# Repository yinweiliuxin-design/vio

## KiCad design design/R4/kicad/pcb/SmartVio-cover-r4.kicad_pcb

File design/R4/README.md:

# SmartVio R4 设计方案

在线版（含效果图）：https://claude.ai/artifact/BZ7bgUTucvGM85bej3NQhv ，本地 `report/index.html`。

装琴效果图：`report/img/r4-on-violin-showcase.jpg`（你的实拍琴 + R4 模块按 3.18 px/mm 合成）。整机方案（琴 + 模块 + App）：https://claude.ai/artifact/1Rpw8Ssot14Bnj9UHH1J9D

基线是 R3 完整交付包和 `review/R3-2026-10-13/` 的两轮审核。R4 只做让样机装得上、能出声、能安全充电、日常好用的修改，不加功能、不换架构、不加芯片。原 R3 文件一律未改。

| 路径 | 内容 | 状态 |
|---|---|---|
| `DECISIONS.md` | 7 个待定问题的定案 | 定稿 |
| `checks/` | PCM1864 时钟与 SAI、电源 IC 逐脚与封装核对 | 完成 |
| `mechanical/` | 改好的 CadQuery 源、R3→R4 补丁、零件 STEP、装配扫掠结果、`CHANGES.md` | 已重建，0 干涉 |
| `firmware/` | R3→R4 补丁、改动源码、Linux 构建脚本、ELF/BIN/MAP、`CHANGES.md` | 已编译，主机测试全过，硬件测试 0 |
| `eco/` | 原理图 ECO（E-01…E-14）、PCB/FPC ECO（L-01…L-22） | 待在 KiCad 10 执行并跑 ERC/DRC |
| `report/` | 设计方案页与 5 张效果图 | — |
| `tools/` | `photo_r4.html` + `shot_alpha.cjs` 渲染模块俯视透明图，`composite_r4.py <照片> <模块图> <输出目录>` 合成装琴效果图；渲染：`step2mesh.cjs <mechanical 目录> r4mesh` 生成网格，`real_r4.html?view=hero|exploded|internal|section|product` | — |

## 还需要做的事

1. 用万用表量 Kycon STX-353K7A-6N：插入 TRS 插头前后 4–5、5–6 是否导通，决定 R323 和固件 `HP_DETECT_ACTIVE_HIGH`。
2. 在 KiCad 10 执行两份 ECO，跑 ERC/DRC/原理图一致性；画 KEYS6、USB16、AUDIO4 FPC 平面图并做纸样。
3. 用 ESP-IDF 5.4.3 重编 ESP32（需补 sdkconfig）；首次配对新耳机需在 ESP32 加搜索和 NVS 保存。
4. 首样台架：FW-RESET-KILL、续航与关机电流、卡扣/按键/异响/插拔力、扬声器音量。
5. 结构：最坏尺寸链、工程图重出、NTC 预压、琴腔配钻。

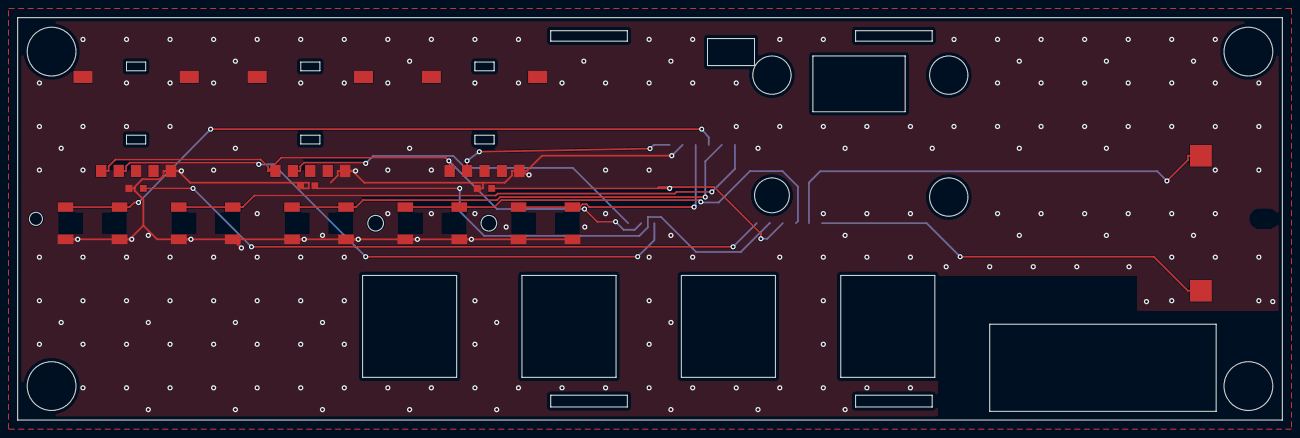
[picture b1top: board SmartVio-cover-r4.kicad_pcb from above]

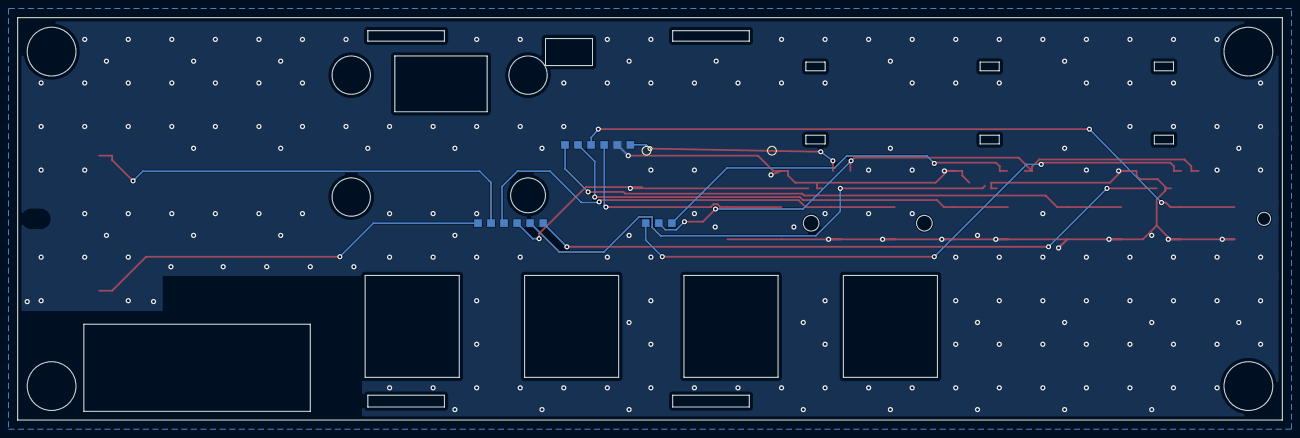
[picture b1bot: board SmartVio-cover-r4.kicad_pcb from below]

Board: 2 copper layers, 145.2 x 46.2 mm, 23 parts (3 on the bottom side), 15 nets.

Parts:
D850, D851, D852: APT1608VRCXF/A-5MAV; LED_Kingbright_APT1608VRCXF_A_5MAV
H901, H902: NPTH_D1.8
H903, H904, H906: NPTH_D4.4_KO5.4
H905: NPTH_D4.0_KO5.0
H907: NPTH_D1.5
H908: SLOT_2.5x1.5
J3406: KEYS6 remote-end FPC landing (H_COVER_1_R); WirePads_6_P1.5
J3408: COVER6 remote-end FPC landing (H_COVER_2_R); WirePads_6_P1.5
J3410: POTS3 remote-end FPC landing (H_COVER_3_R); WirePads_3_P1.5
LS901: AS01808AO-SC18-WP-R; Speaker_PUI_AS01808AO_SC18_Spring_REFERENCE
RV810, RV811, RV812: RK10J11R0A0L; Pot_Alps_RK10J11R0A0L
SW810, SW811, SW812, SW813, SW814: SKQGABE010; Switch_Alps_SKQGABE010

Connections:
FX_RAW: J3406.1, RV812.2 (WIPER)
GND: D850.1 (K), D851.1 (K), D852.1 (K), J3406.2, RV810.3 (LOW), RV811.3 (LOW), RV812.3 (LOW), SW810.3 (B1), SW810.4 (B2), SW811.3 (B1), SW811.4 (B2), SW812.3 (B1), SW812.4 (B2), SW813.3 (B1), SW813.4 (B2), SW814.3 (B1), SW814.4 (B2)
KEY_BT: J3406.3, SW814.1 (A1), SW814.2 (A2)
KEY_FX: J3406.4, SW810.1 (A1), SW810.2 (A2)
KEY_MIX: J3406.5, SW812.1 (A1), SW812.2 (A2)
KEY_MODE: J3406.6, SW811.1 (A1), SW811.2 (A2)
LED_ZONE_1_A: D850.2 (A), J3408.1
LED_ZONE_2_A: D851.2 (A), J3408.2
LED_ZONE_3_A: D852.2 (A), J3408.3
PWR_PB: J3408.4, SW813.1 (A1), SW813.2 (A2)
SPK_N: J3408.5, LS901.2 (-)
SPK_P: J3408.6, LS901.1 (+)
TONE_RAW: J3410.1, RV811.2 (WIPER)
V3D: J3410.2, RV810.1 (HIGH), RV811.1 (HIGH), RV812.1 (HIGH)
VOL_RAW: J3410.3, RV810.2 (WIPER)

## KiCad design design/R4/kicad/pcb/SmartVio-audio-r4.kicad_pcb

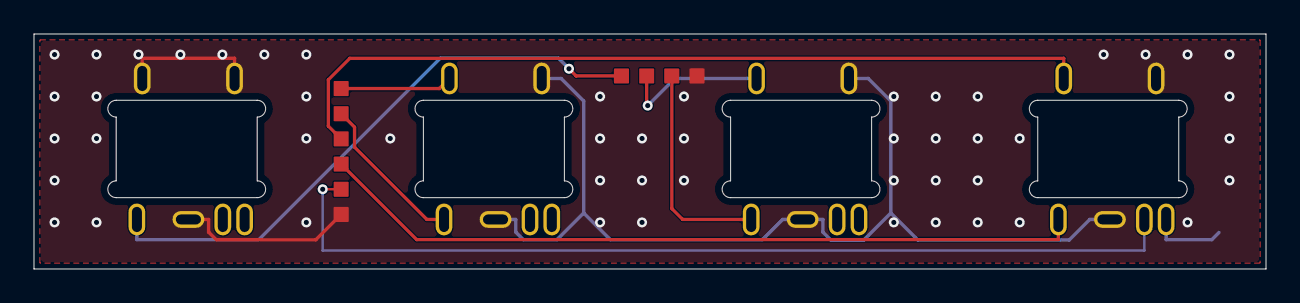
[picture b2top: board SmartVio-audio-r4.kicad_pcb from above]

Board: 2 copper layers, 73.4 x 14.0 mm, 7 parts (1 on the bottom side), 10 nets.

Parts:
J102, J201, J202, J301: STX-353K7A-6N-KTTR; Jack_Kycon_STX353K7A6N
J3402: AUDIO6 remote-end FPC landing (H_AUDIO_1_R); WirePads_6_P1.5
J3404: AUDIO4 remote-end FPC landing (H_AUDIO_2_R); WirePads_4_P1.5
R323: 0R; R_0603_1608Metric

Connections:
GND: J102.1 (SLEEVE), J102.2 (RING2_TRS_SLEEVE), J102.3 (RING1), J201.1 (SLEEVE), J201.2 (RING2_TRS_SLEEVE), J202.1 (SLEEVE), J202.2 (RING2_TRS_SLEEVE), J301.1 (SLEEVE), J301.2 (RING2_TRS_SLEEVE), J3402.1, J3404.4, R323.2
HP_DETECT_RAW: J301.5 (DET_NO_A), J3402.2
HP_DET_B: J301.6 (DET_NO_B), R323.1
HP_L_PORT: J301.4 (TIP), J3402.3
HP_R_PORT: J301.3 (RING1), J3402.4
LINE_L_PORT: J201.4 (TIP), J3402.5
LINE_R_PORT: J201.3 (RING1), J3402.6
RETURN_L_PORT: J202.4 (TIP), J3404.1
RETURN_R_PORT: J202.3 (RING1), J3404.2
SEND_T_PORT: J102.4 (TIP), J3404.3

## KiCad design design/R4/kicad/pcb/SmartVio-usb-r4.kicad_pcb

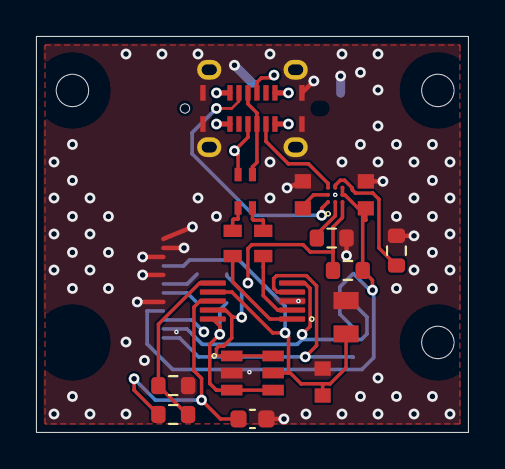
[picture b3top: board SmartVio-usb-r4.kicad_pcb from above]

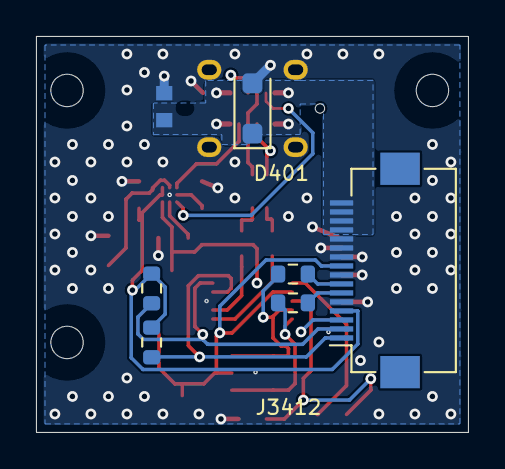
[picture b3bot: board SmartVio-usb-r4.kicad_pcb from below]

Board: 4 copper layers, 24.0 x 22.0 mm, 28 parts (7 on the bottom side), 24 nets.

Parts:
C401, C1401: 100nF / 50V X7R; CC0603KRX7R9BB104
C403: 100nF / 10V X7R; local U401.5 bypass; CC0603KRX7R7BB104
C1402: 1uF / 10V; CC0603KRX7R7BB105
C1501: 2.2uF 16V X7R; effective 1..10uF; CC0805KKX7R7BB225
C1502: 1uF 10V X7R; effective 0.3..3uF; C_0603_1608Metric
D401: SMF12A; D_SOD-123F
FL1501: 90 ohm at 100MHz candidate; ACM2012H-900-2P-T06
H401, H402, H403: NPTH 1.8 KO 4.4; NPTH_D1.8_KO4.4
J401: USB4120-03-C; GCT_USB4120_Official_A6
J3412: FH12-16S-0.5SH(55); Hirose_FH12-16S-0.5SH_1x16-1MP_P0.50mm_Horizontal
KO401: KEEPOUT 4.4 F; KEEPOUT_D4.4_F
L1501, L1502: 10nH matched candidate; 0603HP-10NXGRW
R401, R402: 5.1k; R_0603_1608Metric
R403, R404: 0R / tune at PHY; R_0603_1608Metric
R1401, R1502, R1503: 100k; R_0603_1608Metric
R1501: 24.9k 1%; R_0603_1608Metric
R1504: 140k 1%; R_0603_1608Metric
U401: USBLC6-2SC6; ST_USBLC6_2SC6_SOT23_6L_Official
U1401: TPD2S300YFFR; TI_YFF0009_Official
U1501: TPD2S703QDGSRQ1; TI_DGS0010A_Official

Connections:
CC1_PORT: J401.A5 (CC1), U1401.A1 (C_CC1)
CC1_SAFE: R401.1, U1401.B1 (CC1)
CC2_PORT: J401.B5 (CC2), U1401.A3 (C_CC2)
CC2_SAFE: R402.1, U1401.B3 (CC2)
CC_FAULT_N: J3412.3, R1401.1, U1401.C1 (FLT_N)
CC_VBIAS: C1401.1, U1401.A2 (VBIAS)
GND: C401.2, C403.2, C1401.2, C1402.2, C1501.2, C1502.2, D401.2, J401.A1 (GND), J401.A12 (GND), J401.B1 (GND), J401.B12 (GND), J401.SH (SHELL), J3412.5, J3412.8, J3412.10, J3412.11, J3412.12, R401.2, R402.2, R1501.2, U401.2 (GND), U1401.B2 (GND), U1501.3 (GND)
USB_5V_SAFE: C403.1, C1501.1, J3412.9, U401.5 (VBUS), U1501.7 (VPWR)
USB_DATA_DISABLE: J3412.2, R1502.1, U1501.5 (EN_N)
USB_DATA_FAULT_N: J3412.1, R1503.1, U1501.4 (FLT_N)
USB_DM_CMC: FL1501.3 (DM_OUT), L1502.1
USB_DM_CONN: FL1501.2 (DM_IN), J401.A7 (D-), J401.B7 (D-)
USB_DM_MCU: J3412.6, R404.2
USB_DM_OVP_IN: L1502.2, U1501.1 (VD_MINUS)
USB_DM_SYS: R404.1, U401.3 (IO2), U401.4 (IO2), U1501.10 (D_MINUS)
USB_DP_CMC: FL1501.4 (DP_OUT), L1501.1
USB_DP_CONN: FL1501.1 (DP_IN), J401.A6 (D+), J401.B6 (D+)
USB_DP_MCU: J3412.7, R403.2
USB_DP_OVP_IN: L1501.2, U1501.2 (VD_PLUS)
USB_DP_SYS: R403.1, U401.1 (IO1), U401.6 (IO1), U1501.9 (D_PLUS)
USB_OVP_MODE: R1501.1, R1504.2, U1501.6 (MODE)
USB_VREF: C1502.1, R1504.1, U1501.8 (VREF)
V3D: C1402.1, J3412.4, R1401.2, R1502.2, R1503.2, U1401.C2 (VPWR), U1401.C3 (VM)
VBUS_RAW: C401.1, D401.1, J401.A4 (VBUS), J401.A9 (VBUS), J401.B4 (VBUS), J401.B9 (VBUS), J3412.13, J3412.14, J3412.15, J3412.16

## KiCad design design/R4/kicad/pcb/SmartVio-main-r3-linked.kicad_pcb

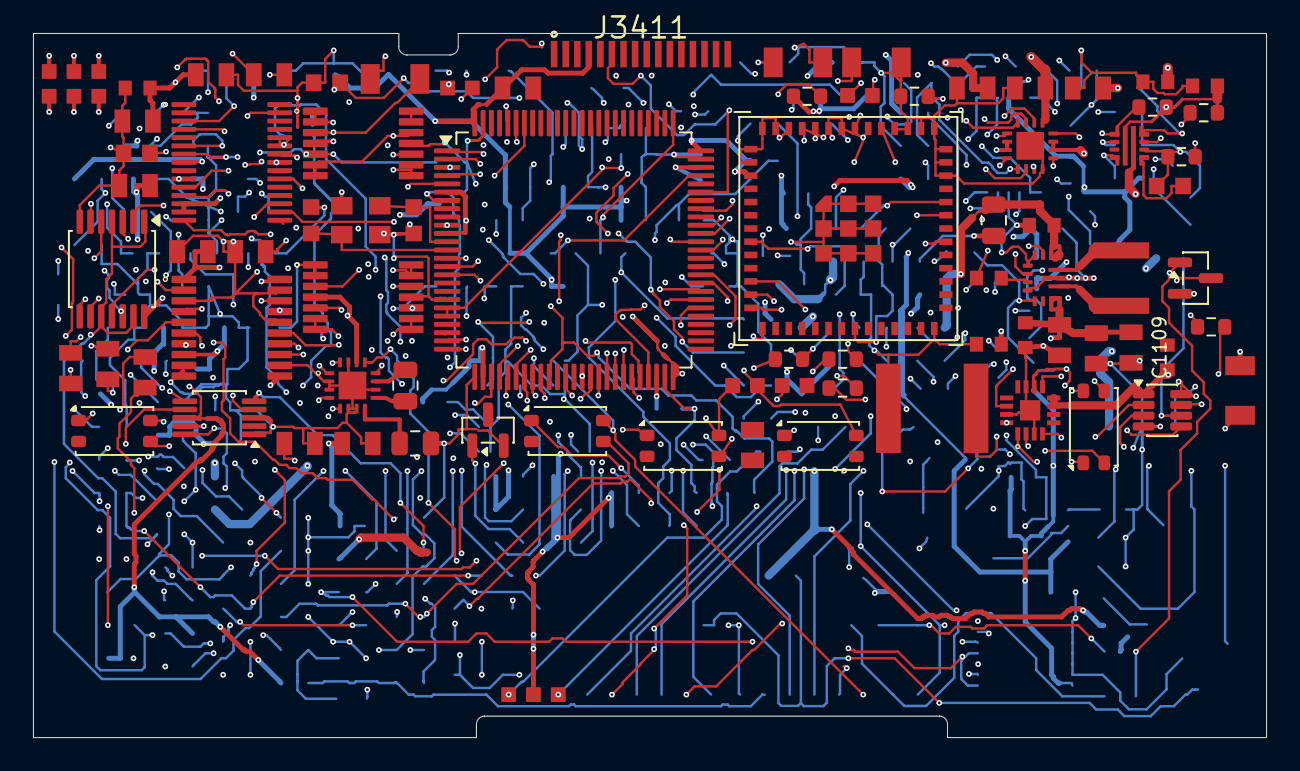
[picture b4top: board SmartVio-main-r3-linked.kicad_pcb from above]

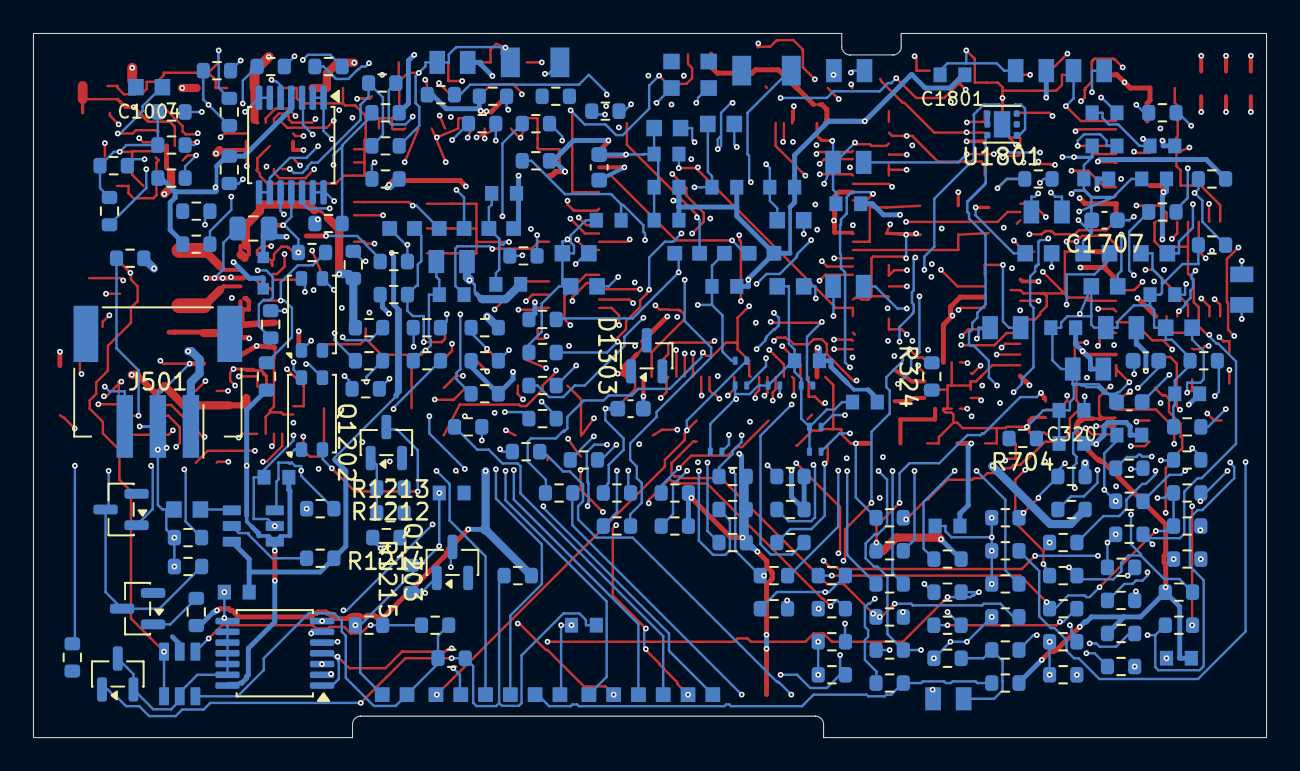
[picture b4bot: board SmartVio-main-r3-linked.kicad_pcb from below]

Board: 8 copper layers, 74.6 x 42.6 mm, 295 parts (217 on the bottom side), 216 nets.

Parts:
C101, C811, C830, C831, C832, C1302: 0.1uF C0G 25V 5%; C1206C104J3GACTU
C102: 10uF / 10V; CC0805KKX5R6BB106
C103, C240, C307, C1301: 100nF / 10V; CC0603KRX7R7BB104
C104, C111, C201, C202, C231, C232, C241, C301, C302: 1uF / 10V; CC0805KKX7R7BB105
C121, C211, C212, C502, C503: 10uF / 10V effective >=4.7uF; CC0805KKX5R6BB106
C221, C222: 4.7uF / 10V; CC0805KKX7R6BB475
C303: 1uF / 10V; C_0805_2012Metric
C304: 2.2uF / 10V X7R; Ceff_min >= C303_Ceff_max; C_0805_2012Metric
C305, C306: 2.2uF / 10V; CC0805KKX7R7BB225
C320: 100nF X7R 10V; CC0603KRX7R7BB104
C501: 4.7uF / 10V effective >=1uF; CC0805KKX7R6BB475
C601, C810, C901: 1uF; CC0603KRX7R7BB105
C602, C604, C606, C608, C703, C710, C712, C714, C801, C802, C803, C804, C805, C809, C902, C904, C1101, C1103, C1107, C1108: 100nF; CC0603KRX7R7BB104
C603, C605, C607, C711, C713, C715, C905: 10uF; CC0805KKX5R6BB106
C701, C702: 2.2uF; C_0603_1608Metric
C704, C705: 0.0022uF C0G 50V 5%; C0603C222J5GACTU
C806: 4.7uF; CC0805KKX7R6BB475
C807, C808: 2.2uF low ESR; C_0603_1608Metric
C812, C813: 3e-05uF C0G 50V 5%; C0603C300J5GACTU
C820: 0.001uF C0G 50V 5%; C0603C102J5GACTU
C821, C822, C823, C824, C825, C1004, C1701, C1702, C1703, C1704, C1705, C1706, C1708, C1901: 0.01uF C0G 25V 5%; C0603C103J3GACTU
C903: 22uF; CC0805MKX5R6BB226
C1001: 0.0047uF C0G 50V 5%; C0603C472J5GACTU
C1002: 100nF 50V; CC0603KRX7R9BB104
C1003: 1uF 16V; CC0603KRX7R7BB105
C1102: 10uF 10V; C_0805_2012Metric
C1104, C1105, C1109: 22uF 10V; CC0805MKX5R6BB226
C1106: 22uF 10V; C_0805_2012Metric
C1303: 0.47uF C0G 50V 5%; C2220C474J5GACTU
C1707: 100pF C0G 50V 5%; C_0603_1608Metric
C1709, C1710, C1711, C1801: 100nF 10V X7R; CC0603KRX7R7BB104
C1902: 2.2uF X7R 16V; effective>=1uF; CC0603KRX7R7BB225
C1903, C1904, C1921, C1922: 100nF X7R 16V; CC0603KRX7R7BB104
D1201, D1202, D1203, D1204, D1205, D1206, D1207: TPD1E10B06DPYR; TI_DPY0002A_1x0.6mm_P0.7mm_NSMD
D1301, D1302: low-leakage enable OR; SOT-23
D1303: BAS116,215; SOT-23
FB1101: Ferrite 120R@100MHz / >=0.5A; 742792625
J101: Existing pickup / polarity TBD; WirePads_2_P1.5
J501: JST PH 3-way internal2A AWG24 pack header; JST_PH_S3B_PH_SM4_TB_OfficialLand_3P
J801: SWD test pads; WirePads_5_P1.5
J901: Speaker harness; WirePads_2_P1.5
J902: RF factory pads - not user connector; WirePads_6_P1.5
J1921: RT1921 harness solder endpoint; WirePads_2_P1.5
J3401: AUDIO6 main-end FPC landing (H_AUDIO_1_M); WirePads_6_P1.5
J3403: AUDIO4 main-end FPC landing (H_AUDIO_2_M); WirePads_4_P1.5
J3405: KEYS6 main-end FPC landing (H_COVER_1_M); WirePads_Control6_2x3_R3
J3407: COVER6 main-end FPC landing (H_COVER_2_M); WirePads_6_P1.5
J3409: POTS3 main-end FPC landing (H_COVER_3_M); WirePads_3_P1.5
J3411: USB16 main-end hot-bar landing (J_USB_M); FPC_USB16_HotBar_Main_P0.70
K1201, K1202: AQY221R6VY; Panasonic_APV-AQY_SSOP-4_4.45x2.65mm_P1.27mm
K1203, K1204, K1205, K1206, K1207: AQY221R2VY; Panasonic_APV-AQY_SSOP-4_4.45x2.65mm_P1.27mm
L1101: 1.5uH / Isat >=5A candidate; XGL4020-152MEC
Q1201, Q1202, Q1203: PMV30UN2R; SOT-23
Q1601: PMV30UN2; SOT-23
R101, R103, R104, R201, R202, R241, R242, R311, R312, R503, R504, R802, R803, R820, R821, R822, R823, R824, R826, R901, R902, R1002, R1004, R1301: 10k; R_0603_1608Metric
R102: 4.7M; R_0603_1608Metric
R111: 100; R_0603_1608Metric
R121, R211, R212: 220; R_0603_1608Metric
R122, R221, R222, R320, R321, R322, R505, R506, R590, R703, R816, R817, R903, R904, R1006, R1104, R1211, R1213, R1215, R1302, R1602: 100k; R_0603_1608Metric
R231, R232, R301, R302: 22k; R_0603_1608Metric
R290, R291: 15k; R_0603_1608Metric
R324, R704, R830, R831, R832, R850, R851, R852, R1210, R1212, R1214, R1603, R1604: 1k; R_0603_1608Metric
R501: 2000ohm 0.1% 25ppm/C; R_0603_1608Metric
R502: 1500ohm 0.1% 25ppm/C; R_0603_1608Metric
R601: 0R; R_0603_1608Metric
R602, R603: 4.7k; R_0603_1608Metric
R691, R810, R811, R812, R813, R814, R815, R906: 33R initial; R_0603_1608Metric
R701, R702, R907: 470R; R_0603_1608Metric
R801: 10R; R_0603_1608Metric
R905: 2k; R_0603_1608Metric
R1001: 26.1k; R_0603_1608Metric
R1003: 39.2k 1%; R_0603_1608Metric
R1005: 2.49k 1%; R_0603_1608Metric
R1101: 312k; 0.1%; <=25ppm/K; exact MPN pending; R_0603_1608Metric
R1102: 100k; 0.1%; <=25ppm/K; exact MPN pending; R_0603_1608Metric
R1103, R1705, R1709: 2.2M 1%; R_0603_1608Metric
R1201, R1202, R1203, R1204, R1205, R1206, R1207: 390R; R_0603_1608Metric
R1303: 33k 1%; R_0603_1608Metric
R1304: 4.7M 1%; R_0603_1608Metric
R1601: 4.7k 1%; R_0603_1608Metric
R1701: 15k 0.1% 25ppm/C; R_0603_1608Metric
R1702: 10k 0.1% 25ppm/C; R_0603_1608Metric
R1703: 100k 0.1% 25ppm/C; R_0603_1608Metric
R1704, R1708, R1712, R1716: 100R 1%; R_0603_1608Metric
R1706, R1710: 1.5M 1%; R_0603_1608Metric
R1707, R1711: 10M 1%; R_0603_1608Metric
R1715: 10M; 1%; ISET buffer bias, include in mirror cali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; R_0603_1608Metric
R1717, R1911, R1913, R1922: 100k 1%; R_0603_1608Metric
R1801, R1802: 33R 1%; R_0603_1608Metric
R1901, R1902, R1903, R1912: 1k 1%; R_0603_1608Metric
R1921: 158k 1%; R_0603_1608Metric
R1923: 8.2k 1%; R_0603_1608Metric
R1924: 30.1k 1%; R_0603_1608Metric
R2351: 3.32k 0.1% 25ppm/C; R_0603_1608Metric
R2352: 68100ohm 0.1% 25ppm/C; R_0603_1608Metric
U101, U201: TLV9064PWR; TI_PW0014A_Official
U301: TPA6132A2RTER; TI_RTE0016C_Official
U501: BQ24074RGTR; TI_RGT0016C_BQ24074_EP17
U601: PCM1864DBTR; TI_DBT0030A_Official
U701: PCM5102APWR; TI_PW0020A_Official
U801: STM32H743VIT6; LQFP-100_14x14mm_P0.5mm
U901: ESP32-MINI-1U
U902: MAX98357AETE+; ADI_T1633_4_Official
U1001: TPS259470LRPWR; TI_RPW0010A_TPS259470
U1101: TPS63070RNMR; TI_RNM0015A_TPS63070
U1301: LTC2954ITS8-1#TRPBF; TSOT-23-8
U1701: ADS1115IDGSR; MSOP-10_3x3mm_P0.5mm
U1702: TMUX1511PWR; TSSOP-14_4.4x5mm_P0.65mm
U1703: OPA4330AIPWR; TSSOP-14_4.4x5mm_P0.65mm
U1801: TMP117AIDRVR; WSON-6-1EP_2x2mm_P0.65mm_EP1x1.6mm
U1901: sequenced performance-domain supply; TI_DBV0006A_Official
U1902: audio I2C powered-domain isolation; TSSOP-14_4.4x5mm_P0.65mm
U1921: independent pack NTC window inhibits charge gate; TI_DDC0006A_Official
U1922: 2.5V independent NTC excitation reference; SOT-23
Y801: 24.576MHz CL18pF candidate; ABM8-24_576MHZ-B2-T

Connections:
ADC_1V8: C602.1, C603.1, U601.11 (LDO)
ADC_AUX_L_AC: C231.2, U601.4 (VINR1)
ADC_AUX_R_AC: C232.2, U601.29 (VINL3)
ADC_BCK: R811.2, U601.17 (BCK)
ADC_BCK_SRC: R811.1, U801.4 (PE5_SAI1SCK)
ADC_DATA: U601.18 (DOUT), U801.5 (PE6_SAI1SD)
ADC_DATA2: R691.2, U801.2 (PE3_SAI1_SD_B)
ADC_DATA2_SRC: R691.1, U601.21 (GPIO1)
ADC_FS: R810.2, U601.16 (LRCK)
ADC_FS_SRC: R810.1, U801.3 (PE4_SAI1FS)
ADC_PU_AC: C111.2, U601.3 (VINL1)
ADC_SCK: R812.2, U601.15 (SCKI)
ADC_SCK_SRC: R812.1, U801.66 (PC9_MCO2)
ADC_VREF: C601.1, U601.6 (VREF)
ADC_XI: R601.1, U601.10 (XI)
AUDIO_BUS_EN: R1913.1, U801.7 (PC13), U1902.1 (SEL1), U1902.4 (SEL2)
AUDIO_PWR_EN: R1911.1, U801.1 (PE2_AUDIO_PWR_EN), U1901.3 (ON)
BOOT0: R803.1, U801.94 (BOOT0)
BUCK_AUX: C1101.1, U1101.3 (VAUX)
BUCK_FB: R1101.2, R1102.1, U1101.5 (FB)
BUCK_L1: L1101.1, U1101.11 (L1)
BUCK_L2: L1101.2, U1101.9 (L2)
CC_FAULT_N: J3411.3, U801.38 (PE8_CC_FAULT_N)
CELL_NTC_SENSE: J1921.1 (NTC_SENSE), R1921.1, R1924.2, U1921.3 (INA+)
CHARGE_ALLOW: R1601.1, U801.44 (PE14_CHARGE_ALLOW)
CHARGE_DISABLE: Q1601.3 (D), R503.2, U501.4 (CE)
CHARGE_GATE: Q1601.1 (G), R1601.2, R1602.1, U1921.1 (OUTA), U1921.6 (OUTB)
CHG_EN1: R590.1, R1603.2, U501.6 (EN1)
CHG_EN1_MCU: R1603.1, U801.42 (PE12_CHG_EN1)
CHG_EN2: R504.2, R1604.2, U501.5 (EN2)
CHG_EN2_MCU: R1604.1, U801.43 (PE13_CHG_EN2)
CHG_ITERM_ECO: R2351.1, U501.15 (ITERM)
CHG_PGOOD_N: R1902.2, U801.47 (PB11_CHG_PGOOD)
CHG_STATUS_N: R1903.2, U801.57 (PD10_CHG_STATUS)
CHG_TMR_ECO: R2352.1, U501.14 (TMR)
CHG_TP: R506.2, R1903.1, U501.9 (CHG)
DAC_1V8: C703.1, U701.18 (LDOO)
DAC_CPN: C701.2, U701.4 (CAPM)
DAC_CPP: C701.1, U701.2 (CAPP)
DAC_L: C201.1, C704.1, R301.1, R701.2
DAC_NEG: C702.1, U701.5 (VNEG)
DAC_R: C202.1, C705.1, R302.1, R702.2
DAC_RAW_L: R701.1, U701.6 (OUTL)
DAC_RAW_R: R702.1, U701.7 (OUTR)
DAC_UNMUTE: R703.1, R704.2, U701.17 (XSMT)
DAC_UNMUTE_MCU: R704.1, U801.22 (PA0)
EFUSE_DVDT: C1001.1, U1001.7 (DVDT)
EFUSE_ILM: R1005.1, U1001.9 (ILM)
EFUSE_ITIMER: C1004.1, U1001.10 (ITIMER)
FX_ADC: C832.1, R832.2, U801.16 (PC1_ADC123_INP11)
FX_RAW: J3405.1, R832.1
GND: C102.2, C103.2, C104.2, C240.2, C241.2, C304.2, C305.2, C306.2, C307.2, C320.2, C501.2, C502.2, C503.2, C601.2, C602.2, C603.2, C604.2, C605.2, C606.2, C607.2, C608.2, C702.2, C703.2, C704.2, C705.2, C710.2, C711.2, C712.2, C713.2, C714.2, C715.2, C801.2, C802.2, C803.2, C804.2, C805.2, C806.2, C807.2, C808.2, C809.2, C810.2, C811.2, C812.2, C813.2, C820.2, C821.2, C822.2, C823.2, C824.2, C825.2, C830.2, C831.2, C832.2, C901.2, C902.2, C903.2, C904.2, C905.2, C1001.2, C1002.2, C1003.2, C1004.2, C1101.2, C1102.2, C1103.2, C1104.2, C1105.2, C1106.2, C1107.2, C1108.2, C1109.2, C1301.2, C1302.2, C1303.2, C1701.2, C1702.2, C1703.2, C1704.2, C1705.2, C1706.2, C1707.2, C1708.2, C1709.2, C1710.2, C1711.2, C1801.2, C1901.2, C1902.2, C1903.2, C1904.2, C1921.2, C1922.2, D1201.2 (GND), D1202.2 (GND), D1203.2 (GND), D1204.2 (GND), D1205.2 (GND), D1206.2 (GND), D1207.2 (GND), J101.2, J501.2 (PACK-), J801.3 (GND), J902.2 (GND), J1921.2 (RETURN), J3401.1, J3403.4, J3405.2, J3411.5, J3411.8, J3411.10, J3411.11, J3411.12, Q1201.2 (S), Q1202.2, Q1203.2, Q1601.2 (S), R104.2, R122.2, R221.2, R222.2, R311.2, R312.2, R320.2, R501.2, R502.2, R504.1, R601.2, R703.2, R803.2, R817.2, R901.2, R904.2, R1002.2, R1004.2, R1005.2, R1102.2, R1211.2, R1213.2, R1215.2, R1302.2, R1304.2, R1602.2, R1702.2, R1703.2, R1706.2, R1707.2, R1710.2, R1711.2, R1715.2, R1717.2, R1911.2, R1913.2, R1922.2, R2351.2, R2352.2, U101.11 (V-), U201.11 (V-), U301.2 (INL+), U301.3 (INR+), U301.6 (G0), U301.7 (G1), U301.10 (PGND), U301.15 (SGND), U301.17 (PAD), U501.8 (VSS), U501.17 (PAD_GND), U601.7 (AGND), U601.12 (DGND), U601.25 (MS_AD), U601.26 (MD0), U701.3 (CPGND), U701.9 (AGND), U701.10 (DEMP), U701.12 (SCK), U701.16 (FMT), U701.19 (DGND), U801.10 (VSS), U801.19 (VSSA), U801.26 (VSS), U801.49 (VSS), U801.74 (VSS), U801.99 (VSS), U901.1 (GND), U901.2 (GND), U901.27 (GND), U901.38 (GND), U901.39 (GND), U901.40 (GND), U901.41 (GND), U901.42 (GND), U901.43 (GND), U901.44 (GND), U901.45 (GND), U901.46 (GND), U901.47 (GND), U901.48 (GND), U901.49 (GND), U901.50 (GND), U901.51 (GND), U901.52 (GND), U901.53 (GND), U901.54 (GND), U901.55 (GND), U902.3 (GND), U902.11 (GND), U902.15 (GND), U902.17 (PAD), U1001.8 (GND), U1101.1 (PS_SYNC), U1101.4 (GND), U1101.10 (PGND), U1101.15 (VSEL), U1301.4 (GND), U1701.1 (ADDR), U1701.3 (GND), U1702.7 (GND), U1703.11 (V_MINUS), U1801.2, U1901.2 (GND), U1902.7 (GND), U1902.8 (D3), U1902.9 (S3), U1902.10 (SEL3), U1902.11 (D4), U1902.12 (S4), U1902.13 (SEL4), U1921.2 (GND), U1922.2 (ANODE), U1922.3 (STAR_TIE_ANODE), Y801.2 (GND), Y801.4 (GND)
HP_ATT_L: C301.1, R301.2, R311.1
HP_ATT_R: C302.1, R302.2, R312.1
HP_CPN: C303.2, U301.9 (CPN)
HP_CPP: C303.1, U301.11 (CPP)
HP_DETECT_GPIO: C320.1, R322.2, U801.28 (PA4)
HP_DETECT_RAW: J3401.2, R321.2, R322.1
HP_EN_MCU: R324.1, U801.23 (PA1)
HP_EN_VALIDATED: R320.1, R324.2, U301.13 (EN)
HP_IN_L: C301.2, U301.1 (INL-)
HP_IN_R: C302.2, U301.4 (INR-)
HP_L: K1201.3 (LOAD_A), U301.16 (OUTL)
HP_L_PORT: D1201.1 (IO), J3401.3, K1201.4 (LOAD_B)
HP_NEG: C304.1, U301.8 (HPVSS)
HP_PORT_ENABLE: R1212.1, U801.61 (PD14)
HP_POS: C305.1, U301.12 (HPVDD)
HP_R: K1202.3 (LOAD_A), U301.5 (OUTR)
HP_R_PORT: D1202.1 (IO), J3401.4, K1202.4 (LOAD_B)
HSE_IN: C812.1, U801.12 (PH0_OSC), Y801.1 (X1)
HSE_OUT: C813.1, U801.13 (PH1_OSC), Y801.3 (X2)
I2C_AUDIO_SCL: U601.24 (SCL), U1902.6 (D2)
I2C_AUDIO_SDA: U601.23 (SDA), U1902.3 (D1)
I2C_SCL: R603.1, R1801.1, U801.95 (PB8_I2C1SCL), U1701.10 (SCL), U1902.5 (S2)
I2C_SDA: R602.1, R1802.1, U801.96 (PB9_I2C1SDA), U1701.9 (SDA), U1902.2 (S1)
KEY_BT: C825.1, J3405.3, R824.2, U801.15 (PC0_KEY_BT)
KEY_FX: C821.1, J3405.4, R820.1, U801.29 (PA5)
KEY_MIX: C823.1, J3405.5, R822.1, U801.31 (PA7)
KEY_MODE: C822.1, J3405.6, R821.1, U801.30 (PA6)
KEY_PWR: C824.1, R823.1, U801.32 (PC4), U1301.5 (INT_N)
LED_ZONE_1: R850.1, U801.63 (PC6)
LED_ZONE_1_A: J3407.1, R850.2
LED_ZONE_2: R851.1, U801.64 (PC7)
LED_ZONE_2_A: J3407.2, R851.2
LED_ZONE_3: R852.1, U801.65 (PC8)
LED_ZONE_3_A: J3407.3, R852.2
LINE_AC_L: C201.2, R290.1
LINE_AC_R: C202.2, R291.1
LINE_BIAS_L: R201.1, R290.2, U201.3 (IN+_A)
LINE_BIAS_R: R202.1, R291.2, U201.5 (IN+_B)
LINE_BUF_L: C211.1, U201.1 (OUT_A), U201.2 (IN-_A)
LINE_BUF_R: C212.1, U201.6 (IN-_B), U201.7 (OUT_B)
LINE_L: K1203.3 (LOAD_A), R211.2, R221.1
LINE_L_PORT: D1203.1 (IO), J3401.5, K1203.4 (LOAD_B)
LINE_OUT_AC_L: C211.2, R211.1
LINE_OUT_AC_R: C212.2, R212.1
LINE_R: K1204.3 (LOAD_A), R212.2, R222.1
LINE_R_PORT: D1204.1 (IO), J3401.6, K1204.4 (LOAD_B)
LOAD_CT: C1901.1, U1901.4 (CT)
LOAD_QOD: R1912.2, U1901.5 (QOD)
MCU_VDDA: C809.1, C810.1, R801.2, U801.20 (VREF+), U801.21 (VDDA)
MON_BAT_ADC: C1704.1, R1708.2, U1701.5 (AIN1)
MON_BAT_BUF: R1708.1, U1703.6 (IN_B_MINUS), U1703.7 (OUT_B)
MON_BAT_BUF_IN: C1703.1, R1707.1, U1702.6 (D2), U1703.5 (IN_B_PLUS)
MON_BAT_DIV: R1705.2, R1706.1, U1702.5 (S2)
MON_ENABLE: R1717.1, U801.46 (PB10_MON_ENABLE), U1702.1 (SEL1), U1702.4 (SEL2), U1702.10 (SEL3), U1702.13 (SEL4)
MON_ICHG_ADC: C1708.1, R1716.2, U1701.7 (AIN3)
MON_ICHG_BUF: R1716.1, U1703.13 (IN_D_MINUS), U1703.14 (OUT_D)
MON_ICHG_BUF_IN: C1707.1, R1715.1, U1702.11 (D4), U1703.12 (IN_D_PLUS)
MON_SYS_ADC: C1706.1, R1712.2, U1701.6 (AIN2)
MON_SYS_BUF: R1712.1, U1703.8 (OUT_C), U1703.9 (IN_C_MINUS)
MON_SYS_BUF_IN: C1705.1, R1711.1, U1702.8 (D3), U1703.10 (IN_C_PLUS)
MON_SYS_DIV: R1709.2, R1710.1, U1702.9 (S3)
MON_USB_ADC: C1702.1, R1704.2, U1701.4 (AIN0)
MON_USB_BUF: R1704.1, U1703.1 (OUT_A), U1703.2 (IN_A_MINUS)
MON_USB_BUF_IN: C1701.1, R1703.1, U1702.3 (D1), U1703.3 (IN_A_PLUS)
MON_USB_DIV: R1701.2, R1702.1, U1702.2 (S1)
NRST: C811.1, J801.5 (NRST), R802.1, U801.14 (NRST)
NTC_COLD_DIV: R1921.2, R1922.1, U1921.4 (INB-)
PACK_NTC: J501.3 (NTC), U501.1 (TS)
PACK_PLUS: C503.1, J501.1 (PACK+), R1705.1, U501.2 (BAT), U501.3 (BAT)
PGOOD_TP: R505.2, R1902.1, U501.7 (PGOOD)
PLAY_BCK: R815.2, U701.13 (BCK), U901.14 (IO26), U902.16 (BCLK)
PLAY_BCK_SRC: R815.1, U801.60 (PD13_SAI2SCK)
PLAY_DATA: R813.2, U701.14 (DIN), U901.33 (IO22)
PLAY_DATA_SRC: R813.1, U801.58 (PD11_SAI2SD)
PLAY_FS: R814.2, U701.15 (LRCK), U901.13 (IO25), U902.14 (LRCLK)
PLAY_FS_SRC: R814.1, U801.59 (PD12_SAI2FS)
PORT_ENABLE: R1210.1, U801.25 (PA3)
PU_ADC_COUPLE: C111.1, R111.2
PU_BIAS: C101.2, R102.1, U101.3 (IN+_A)
PU_BUF: R111.1, U101.1 (OUT_A), U101.2 (IN-_A), U101.10 (IN+_C)
PWR_BOOT_OK: R1301.1, U801.37 (PE7_BOOT_OK)
PWR_KILL: R1301.2, R1302.1, U1301.8 (KILL)
PWR_LTC_EN: D1301.1 (A), R1103.2, U1301.6 (EN)
PWR_ONT: C1302.1, U1301.3 (ONT)
PWR_PB: D1303.3, J3407.4, R826.2, U1301.2 (PB)
PWR_PB_SENSE: D1303.1, U801.51 (PB12)
PWR_PDT: C1303.1, U1301.7 (PDT)
PZ_LIMIT: C101.1, R101.2
PZ_RAW: J101.1, R101.1
RETURN_L: C221.1, K1206.3 (LOAD_A)
RETURN_L_PORT: D1206.1 (IO), J3403.1, K1206.4 (LOAD_B)
RETURN_R: C222.1, K1207.3 (LOAD_A)
RETURN_R_PORT: D1207.1 (IO), J3403.2, K1207.4 (LOAD_B)
RET_AC_L: C221.2, R231.1
RET_AC_R: C222.2, R232.1
RET_BIAS_L: R231.2, R241.1, U201.10 (IN+_C)
RET_BIAS_R: R232.2, R242.1, U201.12 (IN+_D)
RET_BUF_L: C231.1, U201.8 (OUT_C), U201.9 (IN-_C)
RET_BUF_R: C232.1, U201.13 (IN-_D), U201.14 (OUT_D)
RET_PORT_ENABLE: R1214.1, U801.62 (PD15)
RF_BOOT: J902.5 (BOOT), R902.1, U901.21 (IO0)
RF_CHIP_EN: C901.1, J902.6 (EN), R901.1, R907.2, U901.8 (EN)
RF_ENABLE: R907.1, U801.33 (PC5)
RF_PROG_RX: J902.3 (RX_IN), U901.35 (RXD0)
RF_PROG_TX: J902.4 (TX_OUT), U901.36 (TXD0)
RF_RX: U801.55 (PD8_USART3TX), U901.11 (IO32_UART_RX)
RF_TX: U801.56 (PD9_USART3RX), U901.12 (IO33_UART_TX)
RILIM: R502.1, U501.12 (ILIM)
RISET: R501.1, U501.16 (ISET), U1702.12 (S4)
SEND_AC: C121.2, R121.1
SEND_BUF: C121.1, U101.8 (OUT_C), U101.9 (IN-_C)
SEND_T: K1205.3 (LOAD_A), R121.2, R122.1
SEND_T_PORT: D1205.1 (IO), J3403.3, K1205.4 (LOAD_B)
SPK_DATA: R906.2, U902.1 (DIN)
SPK_DATA_SRC: R906.1, U801.41 (PE11_SAI2_SD_B)
SPK_ENABLE: R905.1, U801.24 (PA2)
SPK_GAIN: R903.1, U902.2 (GAIN_SLOT)
SPK_N: J901.2 (SPK-), J3407.5, U902.10 (OUTN)
SPK_P: J901.1 (SPK+), J3407.6, U902.9 (OUTP)
SPK_SD_PIN: R904.1, R905.2, U902.4 (SD_MODE)
SSR_GATE: Q1201.1 (G), R1210.2, R1211.1
SSR_GATE_HP: Q1202.1, R1212.2, R1213.1
SSR_GATE_RET: Q1203.1, R1214.2, R1215.1
SSR_LED_0: K1201.1 (LED_A), R1201.2
SSR_LED_1: K1202.1 (LED_A), R1202.2
SSR_LED_2: K1203.1 (LED_A), R1203.2
SSR_LED_3: K1204.1 (LED_A), R1204.2
SSR_LED_4: K1205.1 (LED_A), R1205.2
SSR_LED_5: K1206.1 (LED_A), R1206.2
SSR_LED_6: K1207.1 (LED_A), R1207.2
SSR_SINK: K1203.2 (LED_K), K1204.2 (LED_K), K1205.2 (LED_K), Q1201.3 (D)
SSR_SINK_HP: K1201.2 (LED_K), K1202.2 (LED_K), Q1202.3
SSR_SINK_RET: K1206.2 (LED_K), K1207.2 (LED_K), Q1203.3
SWCLK: J801.4 (SWCLK), U801.76 (PA14_SWCLK)
SWDIO: J801.2 (SWDIO), U801.72 (PA13_SWDIO)
SYS: C502.1, C904.1, C905.1, C1102.1, C1103.1, C1301.1, R503.1, R826.1, R903.2, R1103.1, R1709.1, U501.10 (OUT), U501.11 (OUT), U902.7 (VDD), U902.8 (VDD), U1101.12 (VIN), U1101.13 (VIN), U1301.1 (VIN)
SYS_ENABLE: D1301.3 (K), D1302.3 (K), R1304.1, U1101.14 (EN)
TEMP_REF2V5: C1922.1, R1923.2, R1924.1, U1922.1 (CATHODE)
TEMP_SCL: R1801.2, U1801.1
TEMP_SDA: R1802.2, U1801.6
TONE_ADC: C831.1, R831.2, U801.35 (PB1)
TONE_RAW: J3409.1, R831.1
UNUSED_BUF: U101.13 (IN-_D), U101.14 (OUT_D)
USB_5V_SAFE: C501.1, C1003.1, C1921.1, J3411.9, R816.1, R1303.1, R1701.1, R1923.1, U501.13 (IN), U1001.6 (OUT), U1921.5 (VDD)
USB_DATA_DISABLE: J3411.2, U801.40 (PE10_USB_DATA_DISABLE)
USB_DATA_FAULT_N: J3411.1, U801.39 (PE9_USB_DATA_FAULT_N)
USB_DM_MCU: J3411.6, U801.70 (PA11_USBDM)
USB_DP_MCU: J3411.7, U801.71 (PA12_USBDP)
USB_FLT: R1006.1, R1901.1, U1001.4 (FLT)
USB_FLT_MCU: R1901.2, U801.45 (PE15_USB_FLT)
USB_OV: R1003.2, R1004.1, U1001.2 (OVLO)
USB_UV: R1001.2, R1002.1, U1001.1 (EN_UVLO)
USB_WAKE_A: D1302.1 (A), R1303.2
V3A: C103.1, C104.1, C240.1, C241.1, C306.1, C307.1, C604.1, C605.1, C710.1, C711.1, C712.1, C713.1, C1106.1, C1107.1, FB1101.2, R103.1, U101.4 (V+), U201.4 (V+), U301.14 (VDD), U601.8 (AVDD), U701.1 (CPVDD), U701.8 (AVDD)
V3D: C801.1, C802.1, C803.1, C804.1, C805.1, C806.1, C902.1, C903.1, C1104.1, C1105.1, C1108.1, C1109.1, C1709.1, C1710.1, C1711.1, C1801.1, C1902.1, C1904.1, J801.1 (VTREF), J902.1 (3V3), J3409.2, J3411.4, R321.1, R505.1, R506.1, R590.2, R602.2, R603.2, R801.1, R802.2, R820.2, R821.2, R822.2, R823.2, R824.1, R902.2, R1006.2, R1101.1, R1104.2, R1201.1, R1202.1, R1203.1, R1204.1, R1205.1, R1206.1, R1207.1, U801.6 (VBAT), U801.11 (VDD), U801.27 (VDD), U801.50 (VDD), U801.75 (VDD), U801.100 (VDD), U901.3 (3V3), U1101.7 (VOUT), U1101.8 (VOUT), U1701.8 (VDD), U1702.14 (VDD), U1703.4 (V_PLUS), U1801.4, U1801.5, U1901.1 (VIN), U1902.14 (VDD)
V3LOAD: C606.1, C607.1, C608.1, C714.1, C715.1, C1903.1, FB1101.1, R1912.1, U601.13 (DVDD), U601.14 (IOVDD), U701.11 (FLT), U701.20 (DVDD), U1901.6 (VOUT)
V3_PG: R1104.1, U1101.2 (PG)
VBUS_RAW: C1002.1, J3411.13, J3411.14, J3411.15, J3411.16, R1001.1, R1003.1, U1001.5 (IN)
VBUS_SENSE: C820.1, R816.2, R817.1, U801.68 (PA9_VBUS)
VCAP1: C807.1, C808.1, U801.48 (VCAP1), U801.73 (VCAP2)
VMID: R102.2, R201.2, R202.2, R241.2, R242.2, U101.6 (IN-_B), U101.7 (OUT_B), U101.12 (IN+_D)
VMID_DIV: C102.1, R103.2, R104.1, U101.5 (IN+_B)
VOL_ADC: C830.1, R830.2, U801.34 (PB0)
VOL_RAW: J3409.3, R830.1

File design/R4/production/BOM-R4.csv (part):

"# SmartVio R4 首样 BOM（候选，未冻结）。来源：R3 candidate-bom-and-placement.json + design/R4/eco/eco-schematic.json + eco-pcb.json。已与 R4 网表 design/R4/kicad/R4-netlist.xml（2026-10-15 12:58，348 个器件）交叉核对：334 个位号一致，10 个差异（见“R4 网表核对”表）。SCH_DONE：R4 netlist FINAL 2026-10-15: /work/r4/r4-netlist.xml (348 comps, 316 nets); ERC 0 errors/3 warnings (missing new fp SmartVioV26:FPC_USB16, FPC_AUDIO4, FPC_USB16_HotBar_Main_P0.70); eco-verification 142/142 pass; new parts R323(DNP) R324 R704 R1212-R1215 Q1202 Q1203 C1004 C1109 D401(Diode_SMD:D_SOD-123F) D1303; J1801/J1802 removed; inter-board endpoints now symbols on A34 with numeric refs J3401-J3412/FPC3401-FPC3406 (old H_*/J_USB_*/FPC_* names in field Endpoint_ID, map: /work/r4/sch-endpoint-refmap.json) - rename PCB footprint refs accordingly; FPC pads S=main end, T=remote end; H_*/J_USB_M landings and FPC bodies are in_bom=no.。BOM 主体仍以 ECO json + R3 候选 BOM 为准。"
板,位号,单板用量,Value,MPN,厂商,封装,面,DNP,装配方式,状态,状态明细,MPN 确认度,待确认标记,供应商料号候选,3 套需求,损耗,建议订购（3 套+损耗）,损耗规则,R4 变更说明
main,"C101, C811, C830, C831, C832, C1302",6,0.1uF C0G 25V 5%,C1206C104J3GACTU,,Passive_V26_ManufacturerLand:C1206C104J3GACTU,B/F,,SMT,R3 carry-over,R3 沿用×6,R3 候选 BOM 已列（未冻结）,,—（包内无分销商料号）,18,20,38,"片式阻容感：+max(20, 30%)（首样卷带/切带损耗）",
main,"C102, C121, C211, C212, C711, C715, C905",7,10uF 10V X5R 0603 (T=0.8mm),GRM188R61A106KE69D,Murata,0603 (库封装待版图 agent 指定),B,,SMT,R4 change,R4 换料×7,未确认,R4 新料号：ECO 置信度中高，需核实存在与厚度 0.8 mm,—（包内无分销商料号）,21,20,41,"片式阻容感：+max(20, 30%)（首样卷带/切带损耗）",L-17 电池投影区限高：C102 CC0805KKX5R6BB106 0805 → Murata GRM188R61A106KE69D 0603；L-17 电池投影区限高：C121 CC0805KKX5R6BB106 0805 → Murata GRM188R61A106KE69D 0603；L-17 电池投影区限高：C211 CC0805KKX5R6BB106 0805 → Murata GRM188R61A106KE69D 0603；L-17 电池投影区限高：C212 CC0805KKX5R6BB106 0805 → Murata GRM188R61A106KE69D 0603；L-17 电池投影区限高：C711 CC0805KKX5R6BB106 0805 → Murata GRM188R61A106KE69D 0603；L-17 电池投影区限高：C715 CC0805KKX5R6BB106 0805 → Murata GRM188R61A106KE69D 0603；L-17 电池投影区限高：C905 CC0805KKX5R6BB106 0805 → Murata GRM188R61A106KE69D 0603
main,"C103, C240, C307, C320, C602, C604, C606, C608, C703, C710, C712, C714, C801, C802, C803, C804, C805, C809, C902, C904, C1101, C1103, C1107, C1108, C1301, C1709, C1710, C1711, C1801, C1903, C1904, C1921, C1922",33,100nF / 10V | 100nF X7R 10V | 100nF | 100nF 10V X7R | 100nF X7R 16V,CC0603KRX7R7BB104,,Passive_V26_ManufacturerLand:CC0603KRX7R7BB104,B/F,,SMT,R4 change,R3 沿用×31、R4 改值×1、R4 换板×1,R3 候选 BOM 已列（未冻结）,,—（包内无分销商料号）,99,30,129,"片式阻容感：+max(20, 30%)（首样卷带/切带损耗）",E-01 C320: 0.01uF C0G 25V 5% C0603C103J3GACTU → 100nF X7R 10V CC0603KRX7R7BB104；E-08 C902 脚 1 改接 V3LOAD→V3D（网表变化，物料不变）；L-12 sensor 板取消，C1801 并入主板 B 面；E-02 C1921 脚 1 改接 SYS→USB_5V_SAFE（网表变化，物料不变）
main,"C104, C111, C201, C202, C231, C232, C241, C301, C302, C303",10,1uF / 10V,CC0805KKX7R7BB105,,Passive_V26_ManufacturerLand:CC0805KKX7R7BB105 | SmartVioV25:C_0805_2012Metric,B/F,,SMT,R3 carry-over,R3 沿用×10,R3 候选 BOM 已列（未冻结）,,—（包内无分销商料号）,30,20,50,"片式阻容感：+max(20, 30%)（首样卷带/切带损耗）",
main,"C221, C222, C501, C806",4,4.7uF / 10V | 4.7uF / 10V effective >=1uF | 4.7uF,CC0805KKX7R6BB475,,Passive_V26_ManufacturerLand:CC0805KKX7R6BB475,B/F,,SMT,R3 carry-over,R3 沿用×4,R3 候选 BOM 已列（未冻结）,,—（包内无分销商料号）,12,20,32,"片式阻容感：+max(20, 30%)（首样卷带/切带损耗）",
main,"C304, C305, C306",3,2.2uF / 10V X7R; Ceff_min >= C303_Ceff_max | 2.2uF / 10V,CC0805KKX7R7BB225,,SmartVioV25:C_0805_2012Metric | Passive_V26_ManufacturerLand:CC0805KKX7R7BB225,F,,SMT,R3 carry-over,R3 沿用×3,R3 候选 BOM 已列（未冻结）,,—（包内无分销商料号）,9,20,29,"片式阻容感：+max(20, 30%)（首样卷带/切带损耗）",
main,"C502, C503, C603, C605, C607, C713, C1102",7,10uF / 10V effective >=4.7uF | 10uF | 10uF 10V,CC0805KKX5R6BB106,,Passive_V26_ManufacturerLand:CC0805KKX5R6BB106 | SmartVioV25:C_0805_2012Metric,F,,SMT,R3 carry-over,R3 沿用×7,R3 候选 BOM 已列（未冻结）,,—（包内无分销商料号）,21,20,41,"片式阻容感：+max(20, 30%)（首样卷带/切带损耗）",
main,"C601, C810, C901, C1003",4,1uF | 1uF 16V,CC0603KRX7R7BB105,,Passive_V26_ManufacturerLand:CC0603KRX7R7BB105,B/F,,SMT,R3 carry-over,R3 沿用×4,R3 候选 BOM 已列（未冻结）,,—（包内无分销商料号）,12,20,32,"片式阻容感：+max(20, 30%)（首样卷带/切带损耗）",
main,"C701, C702, C807, C808",4,2.2uF | 2.2uF low ESR,CC0603KRX5R6BB225,,SmartVioV25:C_0603_1608Metric,B,,SMT,R3 carry-over,R3 沿用×4,R3 候选 BOM 已列（未冻结）,,—（包内无分销商料号）,12,20,32,"片式阻容感：+max(20, 30%)（首样卷带/切带损耗）",
main,"C704, C705",2,0.0022uF C0G 50V 5%,C0603C222J5GACTU,,Passive_V26_ManufacturerLand:C0603C222J5GACTU,B,,SMT,R3 carry-over,R3 沿用×2,R3 候选 BOM 已列（未冻结）,,—（包内无分销商料号）,6,20,26,"片式阻容感：+max(20, 30%)（首样卷带/切带损耗）",
main,"C812, C813",2,3e-05uF C0G 50V 5%,C0603C300J5GACTU,,Passive_V26_ManufacturerLand:C0603C300J5GACTU,F,,SMT,R3 carry-over,R3 沿用×2,MPN 有，Value 待规范,C812 Value 格式错（3e-05uF=30pF，D6）；C813 Value 格式错（3e-05uF=30pF，D6）,—（包内无分销商料号）,6,20,26,"片式阻容感：+max(20, 30%)（首样卷带/切带损耗）",
main,C820,1,0.001uF C0G 50V 5%,C0603C102J5GACTU,,Passive_V26_ManufacturerLand:C0603C102J5GACTU,B,,SMT,R3 carry-over,R3 沿用×1,R3 候选 BOM 已列（未冻结）,,—（包内无分销商料号）,3,20,23,"片式阻容感：+max(20, 30%)（首样卷带/切带损耗）",
main,"C821, C822, C823, C824, C825, C1004, C1701, C1702, C1703, C1704, C1705, C1706, C1708, C1901",14,0.01uF C0G 25V 5% | 0.01uF C0G 25V,C0603C103J3GACTU,,Passive_V26_ManufacturerLand:C0603C103J3GACTU,?/B/F,,SMT,R4 change,R3 沿用×13、R4 新增×1,R3 候选 BOM 已列（未冻结）,,—（包内无分销商料号）,42,20,62,"片式阻容感：+max(20, 30%)（首样卷带/切带损耗）",E-05 新增 C1004
main,"C903, C1104, C1105, C1106, C1109",5,22uF | 22uF 10V | 22uF 10V X5R 0805,CC0805MKX5R6BB226,,Passive_V26_ManufacturerLand:CC0805MKX5R6BB226 | SmartVioV25:C_0805_2012Metric,?/B/F,,SMT,R4 change,R3 沿用×4、R4 新增×1,R3 候选 BOM 已列（未冻结）,,—（包内无分销商料号）,15,20,35,"片式阻容感：+max(20, 30%)（首样卷带/切带损耗）",E-08 C903 脚 1 改接 V3LOAD→V3D（网表变化，物料不变）；E-09 新增 C1109
main,C1001,1,0.0047uF C0G 50V 5%,C0603C472J5GACTU,,Passive_V26_ManufacturerLand:C0603C472J5GACTU,F,,SMT,R3 carry-over,R3 沿用×1,R3 候选 BOM 已列（未冻结）,,—（包内无分销商料号）,3,20,23,"片式阻容感：+max(20, 30%)（首样卷带/切带损耗）",
main,C1002,1,100nF 50V,CC0603KRX7R9BB104,,Passive_V26_ManufacturerLand:CC0603KRX7R9BB104,F,,SMT,R3 carry-over,R3 沿用×1,R3 候选 BOM 已列（未冻结）,,—（包内无分销商料号）,3,20,23,"片式阻容感：+max(20, 30%)（首样卷带/切带损耗）",
main,C1303,1,0.47uF C0G 50V 5%,C2220C474J5GACTU,,Passive_V26_ManufacturerLand:C2220C474J5GACTU,F,,SMT,R3 carry-over,R3 沿用×1,R3 候选 BOM 已列（未冻结）,,—（包内无分销商料号）,3,20,23,"片式阻容感：+max(20, 30%)（首样卷带/切带损耗）",
main,C1707,1,100pF C0G 50V,C0603C101J5GACTU,,SmartVioV25:C_0603_1608Metric,B,,SMT,R4 change,R4 改值×1,R4 新 MPN（ECO 指定，待供应商确认）,R4 新 MPN：按厂商命名规则由 ECO 给出，需分销商确认有货/规格,—（包内无分销商料号）,3,20,23,"片式阻容感：+max(20, 30%)（首样卷带/切带损耗）",E-13 C1707: 0.01uF C0G 25V 5% C0603C103J3GACTU → 100pF C0G 50V C0603C101J5GACTU
main,C1902,1,2.2uF X7R 16V; effective>=1uF,CC0603KRX7R7BB225,,Passive_V26_ManufacturerLand:CC0603KRX7R7BB225,B,,SMT,R3 carry-over,R3 沿用×1,R3 候选 BOM 已列（未冻结）,,—（包内无分销商料号）,3,20,23,"片式阻容感：+max(20, 30%)（首样卷带/切带损耗）",
main,"D1301, D1302, D1303",3,"low-leakage enable OR | BAS116,215","BAS116,215",,SmartVioV25:SOT-23,?/B,,SMT,R4 change,R3 沿用×2、R4 新增×1,MPN 有，Value 待规范,D1301 Value 为功能描述（D5）：原理图 Value 需改成规格；D1302 Value 为功能描述（D5）：原理图 Value 需改成规格；D1303 Value 为功能描述（D5）：原理图 Value 需改成规格,—（包内无分销商料号）,9,5,14,"小分立件：+max(5, 20%)",E-11 新增 D1303
main,FB1101,1,Ferrite 120R@100MHz / >=0.5A,742792625,,Passive_V26_ManufacturerLand:742792625,B,,SMT,R3 carry-over,R3 沿用×1,MPN 有，Value 待规范,FB1101 Value 为功能描述（D5）：原理图 Value 需改成规格,—（包内无分销商料号）,3,20,23,"片式阻容感：+max(20, 30%)（首样卷带/切带损耗）",
main,J501,1,JST PH 3-way internal2A AWG24 pack header,S3B-PH-SM4-TB(LF)(SN),,SmartVio_Battery_Revision:JST_PH_S3B_PH_SM4_TB_OfficialLand_3P,B,,SMT,R3 carry-over,R3 沿用×1,MPN 有，Value 待规范,J501 Value 为功能描述（D5）：原理图 Value 需改成规格,—（包内无分销商料号）,3,2,5,"机电件：+max(2, 20%)",
main,"K1201, K1202",2,AQY221R6VY,AQY221R6VY,,SmartVioV25:Panasonic_APV-AQY_SSOP-4_4.45x2.65mm_P1.27mm,B/F,,SMT,R3 carry-over,R3 沿用×2,R3 候选 BOM 已列（未冻结）,,—（包内无分销商料号）,6,5,11,"小分立件：+max(5, 20%)",E-03 K1201 脚 2 (LED_K) 改接 SSR_SINK→SSR_SINK_HP（网表变化，物料不变）；E-03 K1202 脚 2 (LED_K) 改接 SSR_SINK→SSR_SINK_HP（网表变化，物料不变）
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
